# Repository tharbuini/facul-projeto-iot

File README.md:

# facul-projeto-iot

Desenvolvimento de Hardware para IoT.

```mermaid
graph TD
    A["Alimentação 5V / USB-C"] --> B{"Módulo Regulador 3.3V"}
    B --> C["ESP32-C3 Microcontrolador"]

    C -- I2C --> D["Sensor BME280 (Temp, Umid, Pressão)"]
    C -- GPIO (ADC) --> E["Sensor MQ-135 (Gases Poluentes)"]
    C -- Serial (UART) --> F["Sensor PMS5003 (Material Particulado)"]
    C -- I2C --> G["Display OLED 0.96"]
    C -- GPIO --> H["Botão de Ação"]

    C -- Wi-Fi --> I["Internet"]
    I -- MQTT/HTTPS --> J["Plataforma IoT (AWS IoT Core, Google Cloud IoT Core)"]
    J -- Armazenamento/Análise --> K["Banco de Dados / Serviço de Análise"]
    K -- Visualização/Alertas --> L["Dashboard Web / Aplicativo Móvel"]

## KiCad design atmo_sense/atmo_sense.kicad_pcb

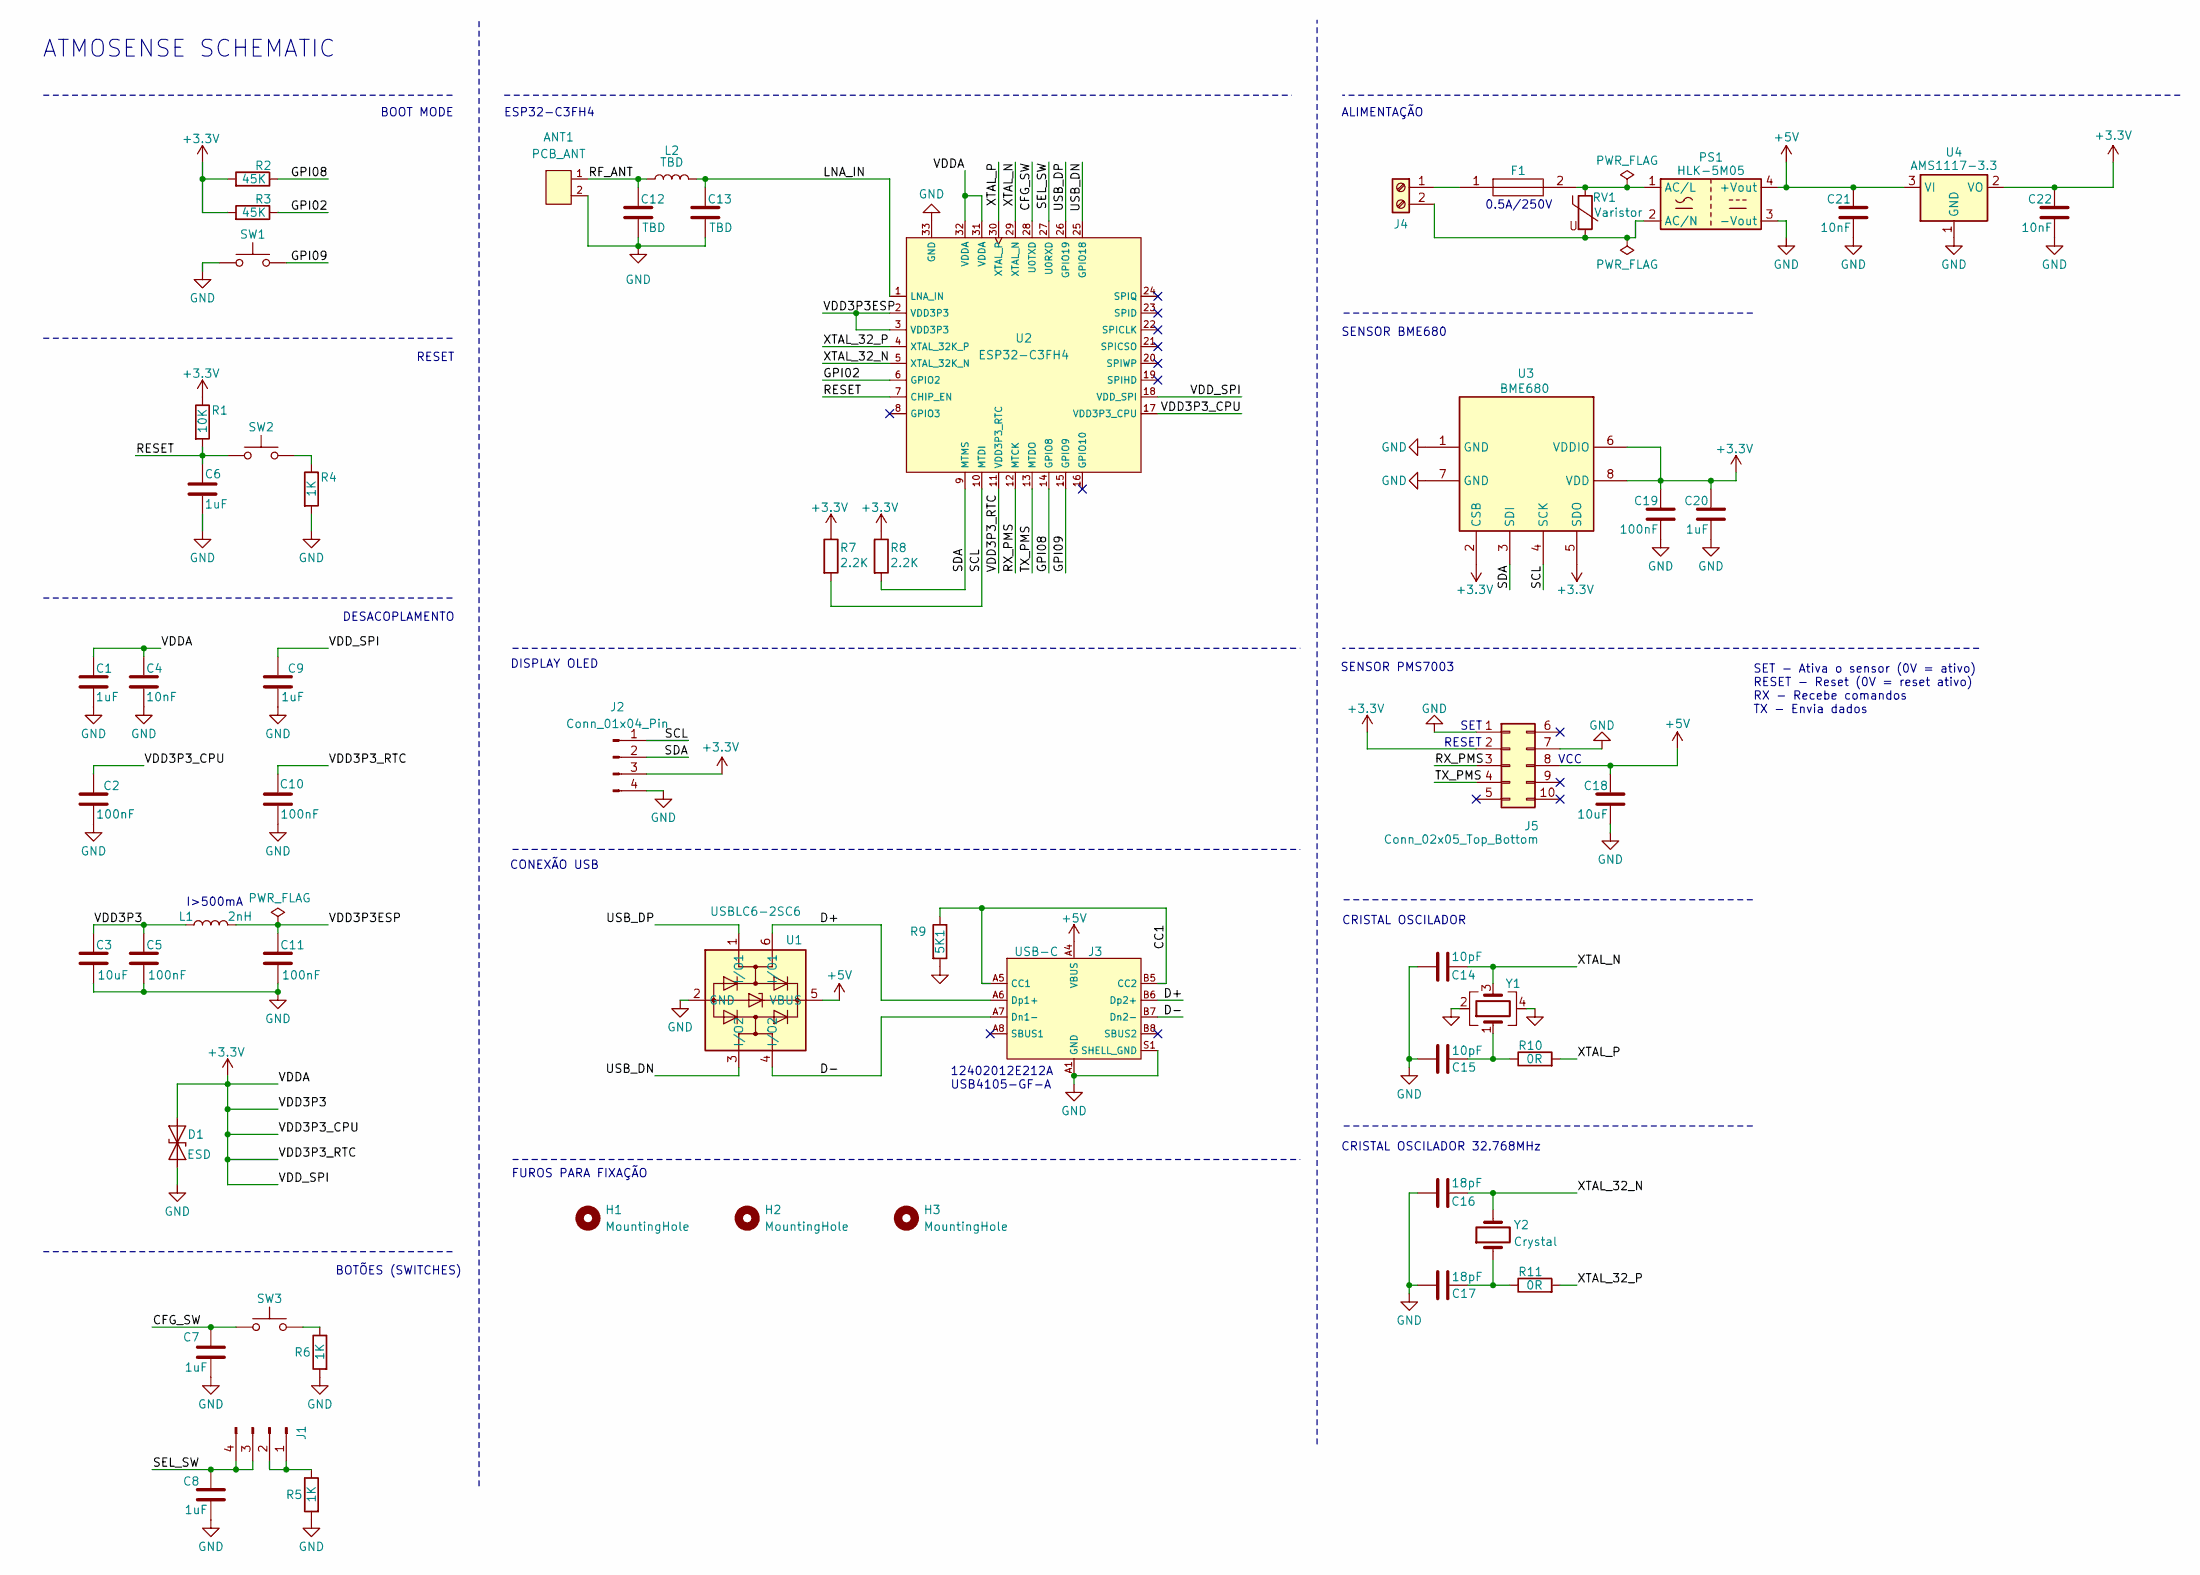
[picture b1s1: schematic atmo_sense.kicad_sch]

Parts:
ANT1: PCB_ANT; Texas_SWRA117D_2.4GHz_Left
C1, C6, C7, C8, C9, C20: 1uF; C_0402_1005Metric
C2, C5, C10, C11, C19: 100nF; C_0402_1005Metric
C3: 10uF; C_0603_1608Metric
C4, C21, C22: 10nF; C_0402_1005Metric
C12, C13: TBD; C_0402_1005Metric
C14, C15: 10pF; C_0402_1005Metric
C16, C17: 18pF; C_0402_1005Metric
C18: 10uF; C_0402_1005Metric
D1: ESD; D_SOD-923
F1: SF-2410SP050W-2; Fuse_2512_6332Metric; Mouser Part Number 652-SF-2410SP050W-2
H1, H2, H3: MountingHole; MountingHole_2mm
J1: Conn_01x04_Pin; PinSocket_2x02_P2.00mm_Vertical
J2: Conn_01x04_Pin; PinSocket_1x04_P2.00mm_Vertical
J3: USB-C; USB_C_Receptacle_XKB_U262-16XN-4BVC11
J4: TB007-508-02BE; TerminalBlock_Phoenix_MKDS-1,5-2-5.08_1x02_P5.08mm_Horizont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
J5: Conn_02x05_Top_Bottom; PinSocket_2x05_P2.00mm_Vertical
L1: 2nH; L_0402_1005Metric
L2: TBD; L_0402_1005Metric
PS1: HLK-5M05; Converter_ACDC_Hi-Link_HLK-5Mxx
R1: 10K; R_0402_1005Metric
R2, R3: 45K; R_0402_1005Metric
R4: 1K; R_0402_1005Metric
R5, R6: 1K; R_0603_1608Metric
R7, R8: 2.2K; R_0402_1005Metric
R9: 5K1; R_0402_1005Metric
R10, R11: 0R; R_0402_1005Metric
RV1: Varistor; RV_Disc_D7mm_W4.3mm_P5mm
SW1, SW2, SW3: SW_Push; SW_SPST_PTS810
U1: USBLC6-2SC6; SOT-23-6
U2: ESP32-C3FH4; QFN-32-1EP_5x5mm_P0.5mm_EP3.7x3.7mm
U3: BME680; Bosch_LGA-8_3x3mm_P0.8mm_ClockwisePinNumbering
U4: AMS1117-3.3; SOT-223-3_TabPin2
Y1: ECS-400-10-36B2-CKM-TR; Crystal_SMD_2520-4Pin_2.5x2.0mm
Y2: Crystal; Crystal_SMD_2520-4Pin_2.5x2.0mm

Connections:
+3.3V: C1.1, C2.1, C3.1, C4.1, C5.1, C9.1, C10.1, C19.1, C20.1, C22.1, D1.2 (A2), J2.3, J5.2, L1.1, R1.1, R2.2, R3.2, R7.1, R8.1, U2.11 (VDD3P3_RTC), U2.17 (VDD3P3_CPU), U2.18 (VDD_SPI), U2.31 (VDDA), U2.32 (VDDA), U3.2 (CSB), U3.5 (SDO), U3.6 (VDDIO), U3.8 (VDD), U4.2 (VO)
+5V: C18.1, C21.1, J3.A4 (VBUS), J3.A9 (VBUS), J3.B4 (VBUS), J3.B9 (VBUS), J5.8, PS1.4 (+Vout), U1.5 (VBUS), U4.3 (VI)
/CC1: J3.A5 (CC1), J3.B5 (CC2), R9.1
/CFG_SW: C7.1, SW3.2, U2.28 (U0TXD)
/D+: J3.A6 (Dp1+), J3.B6 (Dp2+), U1.6 (I/O1)
/D-: J3.A7 (Dn1-), J3.B7 (Dn2-), U1.4 (I/O2)
/GPI02: R3.1, U2.6 (GPIO2)
/GPI08: R2.1, U2.14 (GPIO8)
/GPI09: SW1.1, U2.15 (GPIO9)
/LNA_IN: C13.1, L2.2, U2.1 (LNA_IN)
/RESET: C6.1, R1.2, SW2.1, U2.7 (CHIP_EN)
/RF_ANT: ANT1.1, C12.1, L2.1
/RX_PMS: J5.3, U2.12 (MTCK)
/SCL: J2.1, R7.2, U2.10 (MTDI), U3.4 (SCK)
/SDA: J2.2, R8.2, U2.9 (MTMS), U3.3 (SDI)
/SEL_SW: C8.1, J1.3, J1.4, U2.27 (U0RXD)
/TX_PMS: J5.4, U2.13 (MTDO)
/USB_DN: U1.3 (I/O2), U2.25 (GPIO18)
/USB_DP: U1.1 (I/O1), U2.26 (GPIO19)
/VDD3P3ESP: C11.1, L1.2, U2.2 (VDD3P3), U2.3 (VDD3P3)
/XTAL_32_N: C16.2, U2.5 (XTAL_32K_N), Y2.2
/XTAL_32_P: R11.2, U2.4 (XTAL_32K_P)
/XTAL_N: C14.2, U2.29 (XTAL_N), Y1.3
/XTAL_P: R10.2, U2.30 (XTAL_P)
GND: ANT1.2, C1.2, C2.2, C3.2, C4.2, C5.2, C6.2, C7.2, C8.2, C9.2, C10.2, C11.2, C12.2, C13.2, C14.1, C15.2, C16.1, C17.2, C18.2, C19.2, C20.2, C21.2, C22.2, D1.1 (A1), J2.4, J3.A1 (GND), J3.A12 (GND), J3.B1 (GND), J3.B12 (GND), J3.S1 (SHELL_GND), J5.1, J5.7, PS1.3 (-Vout), R4.2, R5.2, R6.2, R9.2, SW1.2, U1.2 (GND), U2.33 (GND), U3.1 (GND), U3.7 (GND), U4.1 (GND), Y1.2, Y1.4
unnamed: C15.1, R10.1, Y1.1
unnamed: C17.1, R11.1, Y2.1
unnamed: J1.1, J1.2, R5.1
unnamed: F1.1, J4.1
unnamed: J4.2, PS1.2 (AC/N), RV1.2
unnamed: F1.2, PS1.1 (AC/L), RV1.1
unnamed: R4.1, SW2.2
unnamed: R6.1, SW3.1

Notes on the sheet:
SET - Ativa o sensor (0V = ativo) RESET - Reset (0V = reset ativo) RX - Recebe comandos TX - Envia dados
SENSOR BME680
CRISTAL OSCILADOR
CRISTAL OSCILADOR 32.768MHz
SENSOR PMS7003
12402012E212A USB4105-GF-A
ALIMENTAÇÃO
CONEXÃO USB
DISPLAY OLED
ATMOSENSE SCHEMATIC
0.5A/250V
RESET
SET
BOTÕES (SWITCHES)
FUROS PARA FIXAÇÃO
BOOT MODE
I>500mA
DESACOPLAMENTO
ESP32-C3FH4
VCC

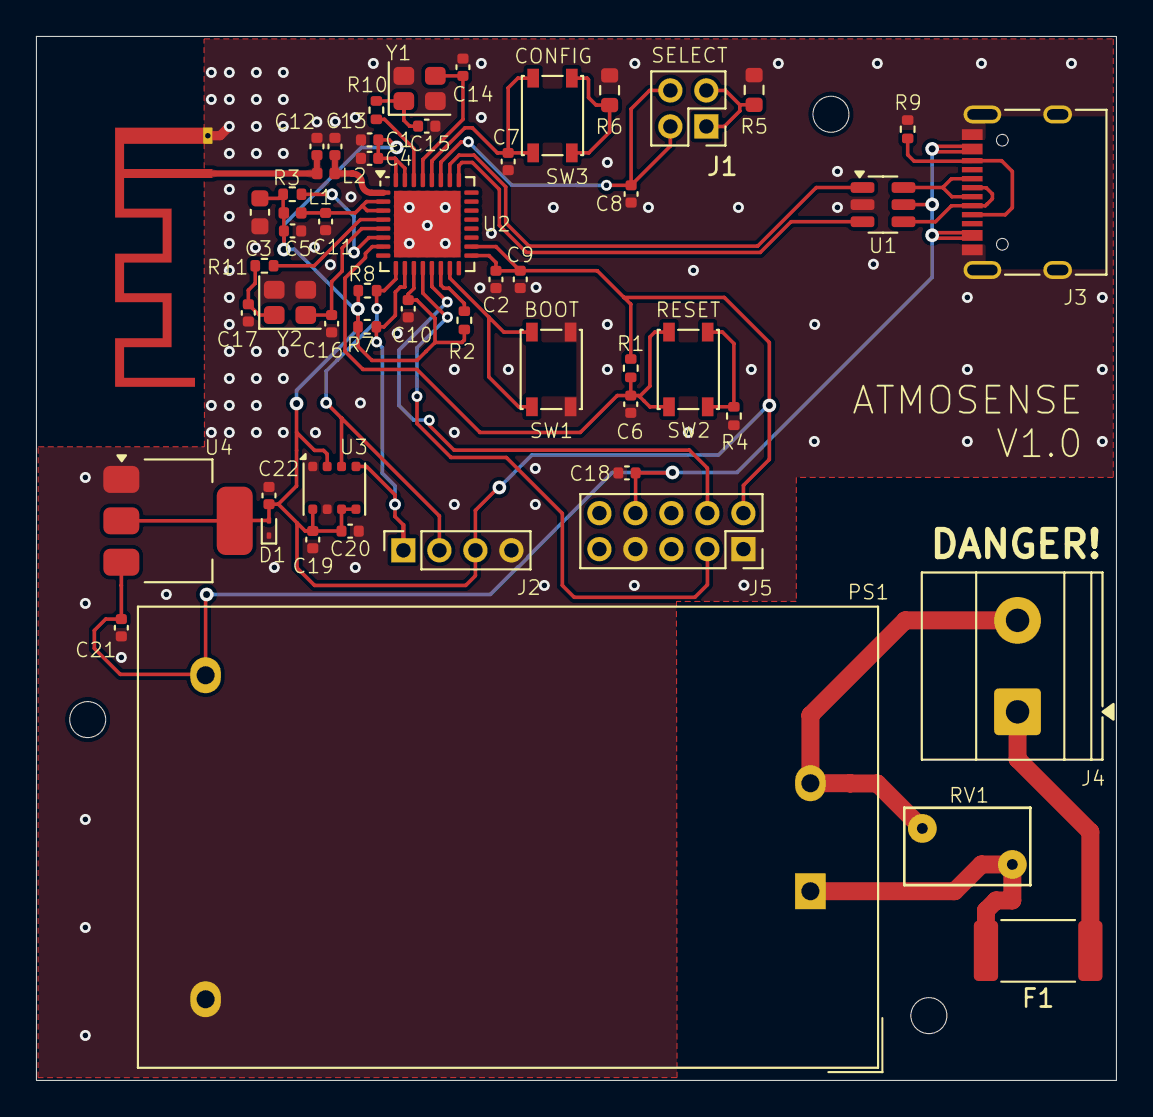
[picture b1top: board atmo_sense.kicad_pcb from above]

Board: 4 copper layers, 60.0 x 58.0 mm, 57 parts (0 on the bottom side), 33 nets.

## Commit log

2025-08-15 Backup inicial
2025-08-18 Backup
2025-08-19 PCB design
